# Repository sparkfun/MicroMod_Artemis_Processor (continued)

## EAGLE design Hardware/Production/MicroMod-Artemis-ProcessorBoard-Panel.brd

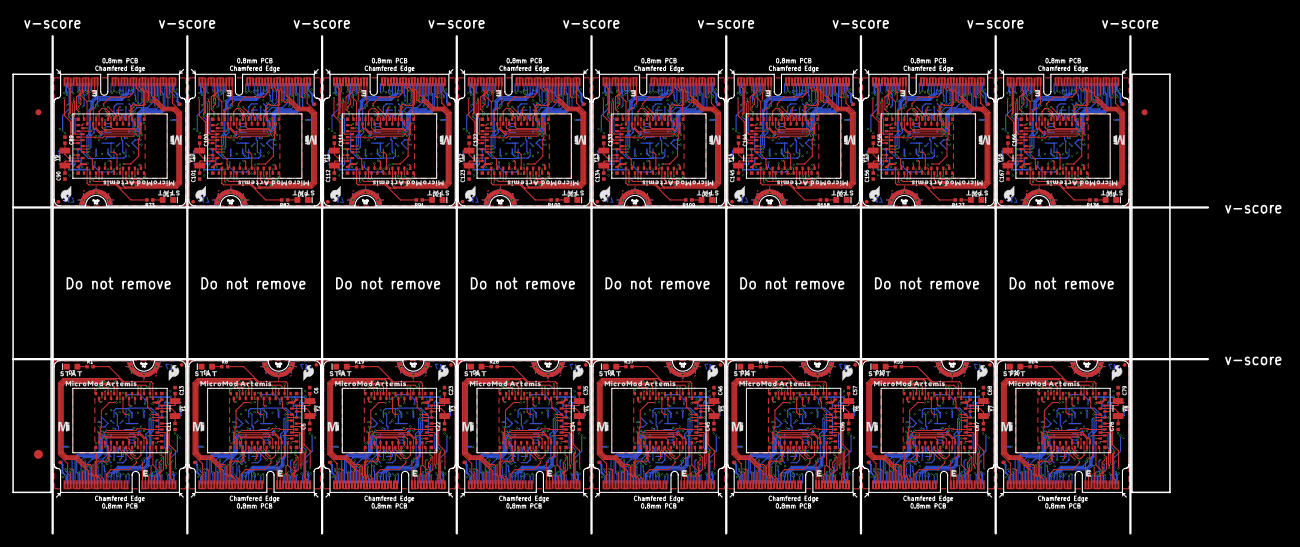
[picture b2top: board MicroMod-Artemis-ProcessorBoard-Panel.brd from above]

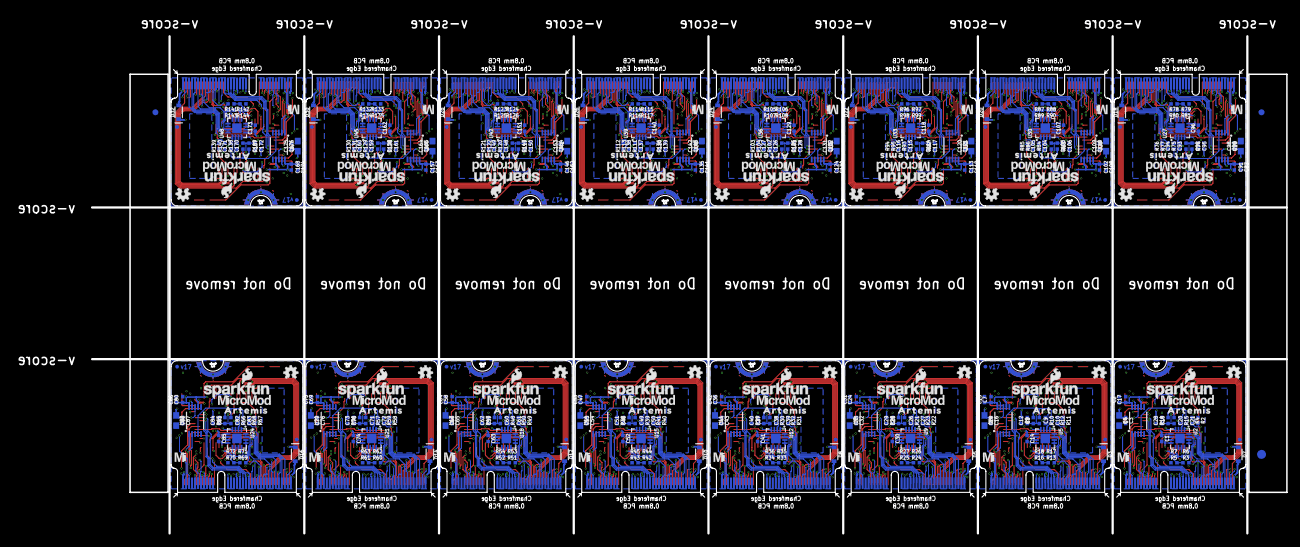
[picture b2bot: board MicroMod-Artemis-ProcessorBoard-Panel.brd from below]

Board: 4 copper layers, 199.6 x 83.1 mm, 646 parts (435 on the bottom side), 1008 nets.

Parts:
C1, C8, C9, C10, C14, C18, C20, C21, C25, C26, C27, C30, C37, C38, C39, C41, C48, C49, C50, C52, C59, C60, C61, C63, C70, C71, C72, C74, C81, C82, C83, C85, C92, C93, C94, C96, C103, C104, C105, C107, C114, C115, C116, C118, C125, C126, C127, C129, C136, C137, C138, C140, C147, C148, C149, C151, C158, C159, C160, C162, C169, C170, C171, C173: 0.1uF; 0402-TIGHT
C2, C15, C31, C42, C53, C64, C75, C86, C97, C108, C119, C130, C141, C152, C163, C174: 0.22uF; 0402-TIGHT
C3, C16, C32, C43, C54, C65, C76, C87, C98, C109, C120, C131, C142, C153, C164, C175: 1.0uF; 0402-TIGHT
C4, C19, C33, C44, C55, C66, C77, C88, C99, C110, C121, C132, C143, C154, C165, C176: 10uF; 0603
C5, C6, C11, C13, C22, C23, C34, C35, C45, C46, C56, C57, C67, C68, C78, C79, C89, C90, C100, C101, C111, C112, C122, C123, C133, C134, C144, C145, C155, C156, C166, C167: 15pF; 0402-TIGHT
C7, C17, C24, C36, C47, C58, C69, C80, C91, C102, C113, C124, C135, C146, C157, C168: 10nF; 0402-TIGHT
C12, C28, C29, C40, C51, C62, C73, C84, C95, C106, C117, C128, C139, C150, C161, C172: 1.0nF; 0402-TIGHT
D1, D2, D4, D6, D9, D11, D13, D15, D17, D19, D21, D23, D25, D27, D29, D31: BLUE; LED-0603
D3, D5, D7, D8, D10, D12, D14, D16, D18, D20, D22, D24, D26, D28, D30, D32: 1A/23V/620mV; SOD-323
E$1, E$2, E$3, E$4: FIDUCIAL-1X2
E$5, E$6: FIDUCIAL-1.5X3
FD1, FD2, FD3, FD4, FD5, FD6, FD7, FD8, FD9, FD10, FD11, FD12, FD13, FD14, FD15, FD16, FD17, FD18, FD19, FD20, FD21, FD22, FD23, FD24, FD25, FD26, FD27, FD28, FD29, FD30, FD31, FD32, FD33, FD34, FD35, FD36, FD37, FD38, FD39, FD40, FD41, FD42, FD43, FD44, FD45, FD46, FD47, FD48, FD49, FD50, FD51, FD52, FD53, FD54, FD55, FD56, FD57, FD58, FD59, FD60, FD61, FD62, FD63, FD64: FIDUCIALUFIDUCIAL; FIDUCIAL-MICRO
J1, J2, J3, J4, J5, J6, J7, J8, J9, J10, J11, J12, J13, J14, J15, J16: MICROMOD-2222; M.2-CARD-E-22
LOGO1, LOGO5, LOGO8, LOGO11, LOGO14, LOGO17, LOGO20, LOGO23, LOGO26, LOGO29, LOGO32, LOGO35, LOGO38, LOGO41, LOGO44, LOGO47: SFE_LOGO_NAME_FLAME.1_INCH; SFE_LOGO_NAME_FLAME_.1
LOGO2, LOGO6, LOGO9, LOGO12, LOGO15, LOGO18, LOGO21, LOGO24, LOGO27, LOGO30, LOGO33, LOGO36, LOGO39, LOGO42, LOGO45, LOGO48: SFE_LOGO_FLAME.1_INCH; SFE_LOGO_FLAME_.1
LOGO3, LOGO4, LOGO7, LOGO10, LOGO13, LOGO16, LOGO19, LOGO22, LOGO25, LOGO28, LOGO31, LOGO34, LOGO37, LOGO40, LOGO43, LOGO46: OSHW-LOGOMINI; OSHW-LOGO-MINI
R1, R8, R19, R28, R37, R46, R55, R64, R73, R82, R91, R100, R109, R118, R127, R136: 1k; 0402-TIGHT
R2, R3, R6, R9, R11, R13, R14, R17, R20, R22, R24, R26, R29, R31, R33, R35, R38, R40, R42, R44, R47, R49, R51, R53, R56, R58, R60, R62, R65, R67, R69, R71, R74, R76, R78, R80, R83, R85, R87, R89, R92, R94, R96, R98, R101, R103, R105, R107, R110, R112, R114, R116, R119, R121, R123, R125, R128, R130, R132, R134, R137, R139, R141, R143: 100k; 0402-TIGHT
R4, R5, R7, R12, R16, R18, R23, R25, R27, R32, R34, R36, R41, R43, R45, R50, R52, R54, R59, R61, R63, R68, R70, R72, R77, R79, R81, R86, R88, R90, R95, R97, R99, R104, R106, R108, R113, R115, R117, R122, R124, R126, R131, R133, R135, R140, R142, R144: 150k; 0402-TIGHT
R10, R15, R21, R30, R39, R48, R57, R66, R75, R84, R93, R102, R111, R120, R129, R138: 220K; 0402-TIGHT
U1, U3, U7, U10, U13, U16, U19, U22, U25, U28, U31, U34, U37, U40, U43, U46: ARTEMIS_MODULESMD; ARTEMIS_FP
U2, U5, U9, U12, U15, U18, U21, U24, U27, U30, U33, U36, U39, U42, U45, U48: TSV524; QFN-16
U4, U6, U8, U11, U14, U17, U20, U23, U26, U29, U32, U35, U38, U41, U44, U47: CH340E_MSOP10; MSOP10
U$1, U$2, U$4, U$7, U$13, U$15, U$19, U$21, U$25, U$27, U$31, U$33, U$37, U$39, U$43, U$45, U$49, U$51, U$55, U$57, U$61, U$63, U$67, U$69, U$73, U$75, U$79, U$81, U$85, U$87, U$91, U$93: MICROMOD_MI_LOGO_.35
U$3, U$5, U$14, U$20, U$26, U$32, U$38, U$44, U$50, U$56, U$62, U$68, U$74, U$80, U$86, U$92: MICROMOD_LOGO_.35
U$6, U$8, U$16, U$22, U$28, U$34, U$40, U$46, U$52, U$58, U$64, U$70, U$76, U$82, U$88, U$94: MICROMOD_ARTEMIS0
U$9, U$10, U$17, U$23, U$29, U$35, U$41, U$47, U$53, U$59, U$65, U$71, U$77, U$83, U$89, U$95: ARTEMIS0
U$11, U$12, U$18, U$24, U$30, U$36, U$42, U$48, U$54, U$60, U$66, U$72, U$78, U$84, U$90, U$96: STAT0
Y1, Y2, Y3, Y4, Y5, Y6, Y7, Y8, Y9, Y10, Y11, Y12, Y13, Y14, Y15, Y16: 32.768kHz; CRYSTAL-SMD-3.2X1.5MM

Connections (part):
3.3V: C2.1, C17.1, C18.1, D7.A, J1.2, J1.74, U6.7, U6.10
3.3V1: C7.1, C8.1, C15.1, D3.A, J2.2, J2.74, U4.7, U4.10
3.3V2: C24.1, C25.1, C31.1, D5.A, J3.2, J3.74, U8.7, U8.10
3.3V3: C36.1, C37.1, C42.1, D8.A, J4.2, J4.74, U11.7, U11.10
3.3V4: C47.1, C48.1, C53.1, D10.A, J5.2, J5.74, U14.7, U14.10
3.3V5: C58.1, C59.1, C64.1, D12.A, J6.2, J6.74, U17.7, U17.10
3.3V6: C69.1, C70.1, C75.1, D14.A, J7.2, J7.74, U20.7, U20.10
3.3V7: C80.1, C81.1, C86.1, D16.A, J8.2, J8.74, U23.7, U23.10
3.3V8: C91.1, C92.1, C97.1, D18.A, J9.2, J9.74, U26.7, U26.10
3.3V9: C102.1, C103.1, C108.1, D20.A, J10.2, J10.74, U29.7, U29.10
3.3V10: C113.1, C114.1, C119.1, D22.A, J11.2, J11.74, U32.7, U32.10
3.3V11: C124.1, C125.1, C130.1, D24.A, J12.2, J12.74, U35.7, U35.10
3.3V12: C135.1, C136.1, C141.1, D26.A, J13.2, J13.74, U38.7, U38.10
3.3V13: C146.1, C147.1, C152.1, D28.A, J14.2, J14.74, U41.7, U41.10
3.3V14: C157.1, C158.1, C163.1, D30.A, J15.2, J15.74, U44.7, U44.10
3.3V15: C168.1, C169.1, C174.1, D32.A, J16.2, J16.74, U47.7, U47.10
3.3V_EN: J1.4, U1.D3
3.3V_EN1: J2.4, U3.D3
3.3V_EN2: J3.4, U7.D3
3.3V_EN3: J4.4, U10.D3
3.3V_EN4: J5.4, U13.D3
3.3V_EN5: J6.4, U16.D3
3.3V_EN6: J7.4, U19.D3
3.3V_EN7: J8.4, U22.D3
3.3V_EN8: J9.4, U25.D3
3.3V_EN9: J10.4, U28.D3
3.3V_EN10: J11.4, U31.D3
3.3V_EN11: J12.4, U34.D3
3.3V_EN12: J13.4, U37.D3
3.3V_EN13: J14.4, U40.D3
3.3V_EN14: J15.4, U43.D3
3.3V_EN15: J16.4, U46.D3
!RESET!: C20.2, C28.1, J1.6, R14.1, U1.~RST
!RESET!1: C9.2, C12.1, J2.6, R9.1, U3.~RST
!RESET!2: C26.2, C29.1, J3.6, R20.1, U7.~RST
!RESET!3: C38.2, C40.1, J4.6, R29.1, U10.~RST
!RESET!4: C49.2, C51.1, J5.6, R38.1, U13.~RST
!RESET!5: C60.2, C62.1, J6.6, R47.1, U16.~RST
!RESET!6: C71.2, C73.1, J7.6, R56.1, U19.~RST
!RESET!7: C82.2, C84.1, J8.6, R65.1, U22.~RST
!RESET!8: C93.2, C95.1, J9.6, R74.1, U25.~RST
!RESET!9: C104.2, C106.1, J10.6, R83.1, U28.~RST
!RESET!10: C115.2, C117.1, J11.6, R92.1, U31.~RST
!RESET!11: C126.2, C128.1, J12.6, R101.1, U34.~RST
!RESET!12: C137.2, C139.1, J13.6, R110.1, U37.~RST
!RESET!13: C148.2, C150.1, J14.6, R119.1, U40.~RST
!RESET!14: C159.2, C161.1, J15.6, R128.1, U43.~RST
!RESET!15: C170.2, C172.1, J16.6, R137.1, U46.~RST
!RTS: C20.1, C21.1, U6.4
!RTS1: C9.1, C10.1, U4.4
!RTS2: C26.1, C27.1, U8.4
!RTS3: C38.1, C39.1, U11.4
!RTS4: C49.1, C50.1, U14.4
!RTS5: C60.1, C61.1, U17.4
!RTS6: C71.1, C72.1, U20.4
!RTS7: C82.1, C83.1, U23.4
!RTS8: C93.1, C94.1, U26.4
!RTS9: C104.1, C105.1, U29.4
!RTS10: C115.1, C116.1, U32.4
!RTS11: C126.1, C127.1, U35.4
!RTS12: C137.1, C138.1, U38.4
!RTS13: C148.1, C149.1, U41.4
!RTS14: C159.1, C160.1, U44.4
!RTS15: C170.1, C171.1, U47.4
ADC0: J1.34, U2.1
ADC0_BUFF1: R3.2, U2.15, U2.16
ADC0_BUFF2: R3.1, R5.2, U2.4
ADC0_BUFF3: R13.1, R16.2, U5.4
ADC0_BUFF4: R13.2, U5.15, U5.16
ADC0_BUFF5: R24.1, R25.2, U9.4
ADC0_BUFF6: R24.2, U9.15, U9.16
ADC0_BUFF7: R33.1, R34.2, U12.4
ADC0_BUFF8: R33.2, U12.15, U12.16
ADC0_BUFF9: R42.1, R43.2, U15.4
ADC0_BUFF10: R42.2, U15.15, U15.16
ADC0_BUFF11: R51.1, R52.2, U18.4
ADC0_BUFF12: R51.2, U18.15, U18.16
ADC0_BUFF13: R60.1, R61.2, U21.4
ADC0_BUFF14: R60.2, U21.15, U21.16
ADC0_BUFF15: R69.1, R70.2, U24.4
ADC0_BUFF16: R69.2, U24.15, U24.16
ADC0_BUFF17: R78.1, R79.2, U27.4
ADC0_BUFF18: R78.2, U27.15, U27.16
ADC0_BUFF19: R87.1, R88.2, U30.4
ADC0_BUFF20: R87.2, U30.15, U30.16
ADC0_BUFF21: R96.1, R97.2, U33.4
ADC0_BUFF22: R96.2, U33.15, U33.16
ADC0_BUFF23: R105.1, R106.2, U36.4
ADC0_BUFF24: R105.2, U36.15, U36.16
ADC0_BUFF25: R114.1, R115.2, U39.4
ADC0_BUFF26: R114.2, U39.15, U39.16
ADC0_BUFF27: R123.1, R124.2, U42.4
ADC0_BUFF28: R123.2, U42.15, U42.16
ADC0_BUFF29: R132.1, R133.2, U45.4
ADC0_BUFF30: R132.2, U45.15, U45.16
ADC0_BUFF31: R141.1, R142.2, U48.4
ADC0_BUFF32: R141.2, U48.15, U48.16
ADC1: J1.38, U2.12
ADC1_BUFF1: R17.1, R18.2, U5.9
ADC1_BUFF2: R6.1, R7.2, U2.9
ADC1_BUFF3: R26.1, R27.2, U9.9
ADC1_BUFF4: R35.1, R36.2, U12.9
ADC1_BUFF5: R44.1, R45.2, U15.9
ADC1_BUFF6: R53.1, R54.2, U18.9
ADC1_BUFF7: R62.1, R63.2, U21.9
ADC1_BUFF8: R71.1, R72.2, U24.9
ADC1_BUFF9: R80.1, R81.2, U27.9
ADC1_BUFF10: R89.1, R90.2, U30.9
ADC1_BUFF11: R98.1, R99.2, U33.9
ADC1_BUFF12: R107.1, R108.2, U36.9
ADC1_BUFF13: R116.1, R117.2, U39.9
ADC1_BUFF14: R125.1, R126.2, U42.9
ADC1_BUFF15: R134.1, R135.2, U45.9
ADC1_BUFF16: R143.1, R144.2, U48.9
ADC2: J2.34, U5.1
ADC3: J2.38, U5.12
ADC4: J3.34, U9.1
ADC5: J3.38, U9.12
ADC6: J4.34, U12.1
ADC7: J4.38, U12.12
ADC8: J5.34, U15.1
ADC9: J5.38, U15.12
ADC10: J6.34, U18.1
ADC11: J6.38, U18.12
ADC12: J7.34, U21.1
ADC13: J7.38, U21.12
ADC14: J8.34, U24.1
ADC15: J8.38, U24.12
ADC16: J9.34, U27.1
ADC17: J9.38, U27.12
ADC18: J10.34, U30.1
ADC19: J10.38, U30.12
ADC20: J11.34, U33.1
ADC21: J11.38, U33.12
ADC22: J12.34, U36.1
ADC23: J12.38, U36.12
ADC24: J13.34, U39.1
ADC25: J13.38, U39.12
ADC26: J14.34, U42.1
ADC27: J14.38, U42.12
ADC28: J15.34, U45.1
ADC29: J15.38, U45.12
ADC30: J16.34, U48.1
ADC31: J16.38, U48.12
ADC_BUFF1: R6.2, U2.13, U2.14
ADC_BUFF2: R17.2, U5.13, U5.14
ADC_BUFF3: R26.2, U9.13, U9.14
ADC_BUFF4: R35.2, U12.13, U12.14
ADC_BUFF5: R44.2, U15.13, U15.14
ADC_BUFF6: R53.2, U18.13, U18.14
ADC_BUFF7: R62.2, U21.13, U21.14
ADC_BUFF8: R71.2, U24.13, U24.14
ADC_BUFF9: R80.2, U27.13, U27.14
ADC_BUFF10: R89.2, U30.13, U30.14
ADC_BUFF11: R98.2, U33.13, U33.14
ADC_BUFF12: R107.2, U36.13, U36.14
ADC_BUFF13: R116.2, U39.13, U39.14
ADC_BUFF14: R125.2, U42.13, U42.14
ADC_BUFF15: R134.2, U45.13, U45.14
ADC_BUFF16: R143.2, U48.13, U48.14
ADC_D+: J1.63, U1.~AD13
ADC_D+1: J2.63, U3.~AD13
ADC_D+2: J3.63, U7.~AD13
ADC_D+3: J4.63, U10.~AD13
ADC_D+4: J5.63, U13.~AD13
ADC_D+5: J6.63, U16.~AD13
ADC_D+6: J7.63, U19.~AD13
ADC_D+7: J8.63, U22.~AD13
ADC_D+8: J9.63, U25.~AD13
ADC_D+9: J10.63, U28.~AD13
ADC_D+10: J11.63, U31.~AD13
ADC_D+11: J12.63, U34.~AD13
ADC_D+12: J13.63, U37.~AD13
ADC_D+13: J14.63, U40.~AD13
ADC_D+14: J15.63, U43.~AD13
ADC_D+15: J16.63, U46.~AD13
BATT_VIN/1: J2.49, R11.2
BATT_VIN/2: J3.49, R22.2
BATT_VIN/3: J1.49, R2.2
BATT_VIN/4: J4.49, R31.2
BATT_VIN/5: J5.49, R40.2
BATT_VIN/6: J6.49, R49.2
BATT_VIN/7: J7.49, R58.2
BATT_VIN/8: J8.49, R67.2
BATT_VIN/9: J9.49, R76.2
BATT_VIN/10: J10.49, R85.2
BATT_VIN/11: J11.49, R94.2
BATT_VIN/12: J12.49, R103.2
BATT_VIN/13: J13.49, R112.2
BATT_VIN/14: J14.49, R121.2
BATT_VIN/15: J15.49, R130.2
BATT_VIN/16: J16.49, R139.2
BOOT: C21.2, J1.11, R15.2, U1.BOOT
BOOT1: C10.2, J2.11, R10.2, U3.BOOT
BOOT2: C27.2, J3.11, R21.2, U7.BOOT
BOOT3: C39.2, J4.11, R30.2, U10.BOOT
BOOT4: C50.2, J5.11, R39.2, U13.BOOT
BOOT5: C61.2, J6.11, R48.2, U16.BOOT
BOOT6: C72.2, J7.11, R57.2, U19.BOOT
BOOT7: C83.2, J8.11, R66.2, U22.BOOT
BOOT8: C94.2, J9.11, R75.2, U25.BOOT
BOOT9: C105.2, J10.11, R84.2, U28.BOOT
BOOT10: C116.2, J11.11, R93.2, U31.BOOT
BOOT11: C127.2, J12.11, R102.2, U34.BOOT
BOOT12: C138.2, J13.11, R111.2, U37.BOOT
BOOT13: C149.2, J14.11, R120.2, U40.BOOT
BOOT14: C160.2, J15.11, R129.2, U43.BOOT
BOOT15: C171.2, J16.11, R138.2, U46.BOOT
CAM_MCLK: J1.56, J1.58, U1.~D18
CAM_MCLK1: J2.56, J2.58, U3.~D18
CAM_MCLK2: J3.56, J3.58, U7.~D18
CAM_MCLK3: J4.56, J4.58, U10.~D18
CAM_MCLK4: J5.56, J5.58, U13.~D18
CAM_MCLK5: J6.56, J6.58, U16.~D18
CAM_MCLK6: J7.56, J7.58, U19.~D18
CAM_MCLK7: J8.56, J8.58, U22.~D18
CAM_MCLK8: J9.56, J9.58, U25.~D18
CAM_MCLK9: J10.56, J10.58, U28.~D18
CAM_MCLK10: J11.56, J11.58, U31.~D18
CAM_MCLK11: J12.56, J12.58, U34.~D18
CAM_MCLK12: J13.56, J13.58, U37.~D18
CAM_MCLK13: J14.56, J14.58, U40.~D18
CAM_MCLK14: J15.56, J15.58, U43.~D18
CAM_MCLK15: J16.56, J16.58, U46.~D18
CAM_PCLK: J1.54, U1.~AD11
CAM_PCLK1: J2.54, U3.~AD11
CAM_PCLK2: J3.54, U7.~AD11
CAM_PCLK3: J4.54, U10.~AD11
CAM_PCLK4: J5.54, U13.~AD11
CAM_PCLK5: J6.54, U16.~AD11
CAM_PCLK6: J7.54, U19.~AD11
CAM_PCLK7: J8.54, U22.~AD11
CAM_PCLK8: J9.54, U25.~AD11
CAM_PCLK9: J10.54, U28.~AD11
CAM_PCLK10: J11.54, U31.~AD11
CAM_PCLK11: J12.54, U34.~AD11
CAM_PCLK12: J13.54, U37.~AD11
CAM_PCLK13: J14.54, U40.~AD11
CAM_PCLK14: J15.54, U43.~AD11
CAM_PCLK15: J16.54, U46.~AD11
CTS1: J1.15, U1.D17
CTS2: J2.15, U3.D17
CTS3: J3.15, U7.D17
CTS4: J4.15, U10.D17
CTS5: J5.15, U13.D17
CTS6: J6.15, U16.D17
CTS7: J7.15, U19.D17
CTS8: J8.15, U22.D17
CTS9: J9.15, U25.D17
CTS10: J10.15, U28.D17
CTS11: J11.15, U31.D17
CTS12: J12.15, U34.D17
CTS13: J13.15, U37.D17
CTS14: J14.15, U40.D17
CTS15: J15.15, U43.D17
CTS16: J16.15, U46.D17
D0: J1.10, U1.D0
D1: J1.18, U1.D1
D2: J2.10, U3.D0
D3: J2.18, U3.D1
D4: J3.10, U7.D0
D5: J3.18, U7.D1
D6: J4.10, U10.D0
D7: J4.18, U10.D1
D8: J5.10, U13.D0
D9: J5.18, U13.D1
D10: J6.10, U16.D0
D11: J6.18, U16.D1
D12: J7.10, U19.D0
D13: J7.18, U19.D1
D14: J8.10, U22.D0
D15: J8.18, U22.D1
D16: J9.10, U25.D0
D17: J9.18, U25.D1
D18: J10.10, U28.D0
D19: J10.18, U28.D1
D20: J11.10, U31.D0
D21: J11.18, U31.D1
D22: J12.10, U34.D0
D23: J12.18, U34.D1
D24: J13.10, U37.D0
D25: J13.18, U37.D1
D26: J14.10, U40.D0
D27: J14.18, U40.D1
D28: J15.10, U43.D0
D29: J15.18, U43.D1
D30: J16.10, U46.D0
D31: J16.18, U46.D1
GND: C1.2, C2.2, C3.2, C4.2, C11.1, C13.1, C17.2, C18.2, C28.2, D2.C, J1.1, J1.7, J1.33, J1.36, J1.39, J1.45, J1.75, J1.GND1, J1.GND2, J1.GND3, R4.1, R5.1, R7.1, R15.1, U1.GND@1, U1.GND@22, U1.GND@38, U1.GND@39, U1.GND@47, U1.GND@59, U2.11, U6.3
GND1: C5.1, C6.1, C7.2, C8.2, C12.2, C14.2, C15.2, C16.2, C19.2, D1.C, J2.1, J2.7, J2.33, J2.36, J2.39, J2.45, J2.75, J2.GND1, J2.GND2, J2.GND3, R10.1, R12.1, R16.1, R18.1, U3.GND@1, U3.GND@22, U3.GND@38, U3.GND@39, U3.GND@47, U3.GND@59, U4.3, U5.11
GND2: C22.1, C23.1, C24.2, C25.2, C29.2, C30.2, C31.2, C32.2, C33.2, D4.C, J3.1, J3.7, J3.33, J3.36, J3.39, J3.45, J3.75, J3.GND1, J3.GND2, J3.GND3, R21.1, R23.1, R25.1, R27.1, U7.GND@1, U7.GND@22, U7.GND@38, U7.GND@39, U7.GND@47, U7.GND@59, U8.3, U9.11
GND3: C34.1, C35.1, C36.2, C37.2, C40.2, C41.2, C42.2, C43.2, C44.2, D6.C, J4.1, J4.7, J4.33, J4.36, J4.39, J4.45, J4.75, J4.GND1, J4.GND2, J4.GND3, R30.1, R32.1, R34.1, R36.1, U10.GND@1, U10.GND@22, U10.GND@38, U10.GND@39, U10.GND@47, U10.GND@59, U11.3, U12.11
GND4: C45.1, C46.1, C47.2, C48.2, C51.2, C52.2, C53.2, C54.2, C55.2, D9.C, J5.1, J5.7, J5.33, J5.36, J5.39, J5.45, J5.75, J5.GND1, J5.GND2, J5.GND3, R39.1, R41.1, R43.1, R45.1, U13.GND@1, U13.GND@22, U13.GND@38, U13.GND@39, U13.GND@47, U13.GND@59, U14.3, U15.11
GND5: C56.1, C57.1, C58.2, C59.2, C62.2, C63.2, C64.2, C65.2, C66.2, D11.C, J6.1, J6.7, J6.33, J6.36, J6.39, J6.45, J6.75, J6.GND1, J6.GND2, J6.GND3, R48.1, R50.1, R52.1, R54.1, U16.GND@1, U16.GND@22, U16.GND@38, U16.GND@39, U16.GND@47, U16.GND@59, U17.3, U18.11
GND6: C67.1, C68.1, C69.2, C70.2, C73.2, C74.2, C75.2, C76.2, C77.2, D13.C, J7.1, J7.7, J7.33, J7.36, J7.39, J7.45, J7.75, J7.GND1, J7.GND2, J7.GND3, R57.1, R59.1, R61.1, R63.1, U19.GND@1, U19.GND@22, U19.GND@38, U19.GND@39, U19.GND@47, U19.GND@59, U20.3, U21.11
GND7: C78.1, C79.1, C80.2, C81.2, C84.2, C85.2, C86.2, C87.2, C88.2, D15.C, J8.1, J8.7, J8.33, J8.36, J8.39, J8.45, J8.75, J8.GND1, J8.GND2, J8.GND3, R66.1, R68.1, R70.1, R72.1, U22.GND@1, U22.GND@22, U22.GND@38, U22.GND@39, U22.GND@47, U22.GND@59, U23.3, U24.11
GND8: C89.1, C90.1, C91.2, C92.2, C95.2, C96.2, C97.2, C98.2, C99.2, D17.C, J9.1, J9.7, J9.33, J9.36, J9.39, J9.45, J9.75, J9.GND1, J9.GND2, J9.GND3, R75.1, R77.1, R79.1, R81.1, U25.GND@1, U25.GND@22, U25.GND@38, U25.GND@39, U25.GND@47, U25.GND@59, U26.3, U27.11
GND9: C100.1, C101.1, C102.2, C103.2, C106.2, C107.2, C108.2, C109.2, C110.2, D19.C, J10.1, J10.7, J10.33, J10.36, J10.39, J10.45, J10.75, J10.GND1, J10.GND2, J10.GND3, R84.1, R86.1, R88.1, R90.1, U28.GND@1, U28.GND@22, U28.GND@38, U28.GND@39, U28.GND@47, U28.GND@59, U29.3, U30.11
GND10: C111.1, C112.1, C113.2, C114.2, C117.2, C118.2, C119.2, C120.2, C121.2, D21.C, J11.1, J11.7, J11.33, J11.36, J11.39, J11.45, J11.75, J11.GND1, J11.GND2, J11.GND3, R93.1, R95.1, R97.1, R99.1, U31.GND@1, U31.GND@22, U31.GND@38, U31.GND@39, U31.GND@47, U31.GND@59, U32.3, U33.11
GND11: C122.1, C123.1, C124.2, C125.2, C128.2, C129.2, C130.2, C131.2, C132.2, D23.C, J12.1, J12.7, J12.33, J12.36, J12.39, J12.45, J12.75, J12.GND1, J12.GND2, J12.GND3, R102.1, R104.1, R106.1, R108.1, U34.GND@1, U34.GND@22, U34.GND@38, U34.GND@39, U34.GND@47, U34.GND@59, U35.3, U36.11
GND12: C133.1, C134.1, C135.2, C136.2, C139.2, C140.2, C141.2, C142.2, C143.2, D25.C, J13.1, J13.7, J13.33, J13.36, J13.39, J13.45, J13.75, J13.GND1, J13.GND2, J13.GND3, R111.1, R113.1, R115.1, R117.1, U37.GND@1, U37.GND@22, U37.GND@38, U37.GND@39, U37.GND@47, U37.GND@59, U38.3, U39.11
GND13: C144.1, C145.1, C146.2, C147.2, C150.2, C151.2, C152.2, C153.2, C154.2, D27.C, J14.1, J14.7, J14.33, J14.36, J14.39, J14.45, J14.75, J14.GND1, J14.GND2, J14.GND3, R120.1, R122.1, R124.1, R126.1, U40.GND@1, U40.GND@22, U40.GND@38, U40.GND@39, U40.GND@47, U40.GND@59, U41.3, U42.11
GND14: C155.1, C156.1, C157.2, C158.2, C161.2, C162.2, C163.2, C164.2, C165.2, D29.C, J15.1, J15.7, J15.33, J15.36, J15.39, J15.45, J15.75, J15.GND1, J15.GND2, J15.GND3, R129.1, R131.1, R133.1, R135.1, U43.GND@1, U43.GND@22, U43.GND@38, U43.GND@39, U43.GND@47, U43.GND@59, U44.3, U45.11
GND15: C166.1, C167.1, C168.2, C169.2, C172.2, C173.2, C174.2, C175.2, C176.2, D31.C, J16.1, J16.7, J16.33, J16.36, J16.39, J16.45, J16.75, J16.GND1, J16.GND2, J16.GND3, R138.1, R140.1, R142.1, R144.1, U46.GND@1, U46.GND@22, U46.GND@38, U46.GND@39, U46.GND@47, U46.GND@59, U47.3, U48.11
GPIO0: J1.40, U1.AD16
GPIO1: J1.42, U1.~AD33/SWO
GPIO2: J1.44, U1.AD34
GPIO3: J1.46, U1.~D27
GPIO4: J1.48, U1.~D28
GPIO5: J1.73, U1.~AD29
GPIO6: J1.71, U1.D14
GPIO7: J1.69, U1.D15
GPIO8: J2.73, U3.~AD29
GPIO9: J2.69, U3.D15
GPIO10: J2.71, U3.D14
GPIO11: J2.42, U3.~AD33/SWO
GPIO12: J2.46, U3.~D27
GPIO13: J2.44, U3.AD34
GPIO14: J2.48, U3.~D28
GPIO15: J2.40, U3.AD16
GPIO16: J3.73, U7.~AD29
GPIO17: J3.69, U7.D15
GPIO18: J3.71, U7.D14
GPIO19: J3.42, U7.~AD33/SWO
GPIO20: J3.46, U7.~D27
GPIO21: J3.44, U7.AD34
GPIO22: J3.48, U7.~D28
GPIO23: J3.40, U7.AD16
GPIO24: J4.73, U10.~AD29
GPIO25: J4.69, U10.D15
GPIO26: J4.71, U10.D14
GPIO27: J4.42, U10.~AD33/SWO
GPIO28: J4.46, U10.~D27
GPIO29: J4.44, U10.AD34
GPIO30: J4.48, U10.~D28
GPIO31: J4.40, U10.AD16
GPIO32: J5.73, U13.~AD29
GPIO33: J5.69, U13.D15
GPIO34: J5.71, U13.D14
GPIO35: J5.42, U13.~AD33/SWO
GPIO36: J5.46, U13.~D27
GPIO37: J5.44, U13.AD34
GPIO38: J5.48, U13.~D28
GPIO39: J5.40, U13.AD16
GPIO40: J6.73, U16.~AD29
GPIO41: J6.69, U16.D15
GPIO42: J6.71, U16.D14
GPIO43: J6.42, U16.~AD33/SWO
GPIO44: J6.46, U16.~D27
GPIO45: J6.44, U16.AD34
GPIO46: J6.48, U16.~D28
GPIO47: J6.40, U16.AD16
GPIO48: J7.73, U19.~AD29
GPIO49: J7.69, U19.D15
GPIO50: J7.71, U19.D14
GPIO51: J7.42, U19.~AD33/SWO
GPIO52: J7.46, U19.~D27
GPIO53: J7.44, U19.AD34
GPIO54: J7.48, U19.~D28
GPIO55: J7.40, U19.AD16
GPIO56: J8.73, U22.~AD29
GPIO57: J8.69, U22.D15
GPIO58: J8.71, U22.D14
GPIO59: J8.42, U22.~AD33/SWO
GPIO60: J8.46, U22.~D27
GPIO61: J8.44, U22.AD34
GPIO62: J8.48, U22.~D28
GPIO63: J8.40, U22.AD16
GPIO64: J9.73, U25.~AD29
GPIO65: J9.69, U25.D15
GPIO66: J9.71, U25.D14
GPIO67: J9.42, U25.~AD33/SWO
GPIO68: J9.46, U25.~D27
GPIO69: J9.44, U25.AD34
GPIO70: J9.48, U25.~D28
GPIO71: J9.40, U25.AD16
GPIO72: J10.73, U28.~AD29
GPIO73: J10.69, U28.D15
GPIO74: J10.71, U28.D14
GPIO75: J10.42, U28.~AD33/SWO
GPIO76: J10.46, U28.~D27
GPIO77: J10.44, U28.AD34
GPIO78: J10.48, U28.~D28
GPIO79: J10.40, U28.AD16
GPIO80: J11.73, U31.~AD29
GPIO81: J11.69, U31.D15
GPIO82: J11.71, U31.D14
GPIO83: J11.42, U31.~AD33/SWO
GPIO84: J11.46, U31.~D27
GPIO85: J11.44, U31.AD34
GPIO86: J11.48, U31.~D28
GPIO87: J11.40, U31.AD16
GPIO88: J12.73, U34.~AD29
GPIO89: J12.69, U34.D15
GPIO90: J12.71, U34.D14
GPIO91: J12.42, U34.~AD33/SWO
GPIO92: J12.46, U34.~D27
GPIO93: J12.44, U34.AD34
GPIO94: J12.48, U34.~D28
GPIO95: J12.40, U34.AD16
GPIO96: J13.73, U37.~AD29
GPIO97: J13.69, U37.D15
GPIO98: J13.71, U37.D14
GPIO99: J13.42, U37.~AD33/SWO
GPIO100: J13.46, U37.~D27
GPIO101: J13.44, U37.AD34
GPIO102: J13.48, U37.~D28
GPIO103: J13.40, U37.AD16
GPIO104: J14.73, U40.~AD29
GPIO105: J14.69, U40.D15
GPIO106: J14.71, U40.D14
GPIO107: J14.42, U40.~AD33/SWO
GPIO108: J14.46, U40.~D27
GPIO109: J14.44, U40.AD34
GPIO110: J14.48, U40.~D28
GPIO111: J14.40, U40.AD16
GPIO112: J15.73, U43.~AD29
GPIO113: J15.69, U43.D15
GPIO114: J15.71, U43.D14
GPIO115: J15.42, U43.~AD33/SWO
GPIO116: J15.46, U43.~D27
GPIO117: J15.44, U43.AD34
GPIO118: J15.48, U43.~D28
GPIO119: J15.40, U43.AD16
GPIO120: J16.73, U46.~AD29
GPIO121: J16.69, U46.D15
GPIO122: J16.71, U46.D14
GPIO123: J16.42, U46.~AD33/SWO
GPIO124: J16.46, U46.~D27
GPIO125: J16.44, U46.AD34
GPIO126: J16.48, U46.~D28
GPIO127: J16.40, U46.AD16
I2C_!INT!: J1.16, U1.D2
I2C_!INT!1: J2.16, U3.D2
I2C_!INT!2: J3.16, U7.D2
I2C_!INT!3: J4.16, U10.D2
I2C_!INT!4: J5.16, U13.D2
I2C_!INT!5: J6.16, U16.D2
I2C_!INT!6: J7.16, U19.D2
I2C_!INT!7: J8.16, U22.D2
I2C_!INT!8: J9.16, U25.D2
I2C_!INT!9: J10.16, U28.D2
I2C_!INT!10: J11.16, U31.D2
I2C_!INT!11: J12.16, U34.D2
I2C_!INT!12: J13.16, U37.D2
I2C_!INT!13: J14.16, U40.D2
I2C_!INT!14: J15.16, U43.D2
I2C_!INT!15: J16.16, U46.D2
LED_BUILTIN: R1.2, U1.~D19
LED_BUILTIN1: R8.2, U3.~D19
LED_BUILTIN2: R19.2, U7.~D19
LED_BUILTIN3: R28.2, U10.~D19
LED_BUILTIN4: R37.2, U13.~D19
LED_BUILTIN5: R46.2, U16.~D19
LED_BUILTIN6: R55.2, U19.~D19
LED_BUILTIN7: R64.2, U22.~D19
LED_BUILTIN8: R73.2, U25.~D19
LED_BUILTIN9: R82.2, U28.~D19
LED_BUILTIN10: R91.2, U31.~D19
LED_BUILTIN11: R100.2, U34.~D19
LED_BUILTIN12: R109.2, U37.~D19
LED_BUILTIN13: R118.2, U40.~D19
LED_BUILTIN14: R127.2, U43.~D19
LED_BUILTIN15: R136.2, U46.~D19
unnamed: C5.2, U3.XO, Y2.P$2
unnamed: D2.A, R1.1
unnamed: D1.A, R8.1
unnamed: C6.2, U3.XI, Y2.P$1
unnamed: C13.2, U1.XI, Y1.P$1
unnamed: C22.2, U7.XO, Y3.P$2
unnamed: C11.2, U1.XO, Y1.P$2
unnamed: D4.A, R19.1
unnamed: C23.2, U7.XI, Y3.P$1
unnamed: C34.2, U10.XO, Y4.P$2
unnamed: D6.A, R28.1
unnamed: C35.2, U10.XI, Y4.P$1
unnamed: C45.2, U13.XO, Y5.P$2
unnamed: D9.A, R37.1
unnamed: C46.2, U13.XI, Y5.P$1
unnamed: C56.2, U16.XO, Y6.P$2
unnamed: D11.A, R46.1
unnamed: C57.2, U16.XI, Y6.P$1
unnamed: C67.2, U19.XO, Y7.P$2
unnamed: D13.A, R55.1
unnamed: C68.2, U19.XI, Y7.P$1
unnamed: C78.2, U22.XO, Y8.P$2
unnamed: D15.A, R64.1
unnamed: C79.2, U22.XI, Y8.P$1
unnamed: C89.2, U25.XO, Y9.P$2
unnamed: D17.A, R73.1
unnamed: C90.2, U25.XI, Y9.P$1
unnamed: C100.2, U28.XO, Y10.P$2
unnamed: D19.A, R82.1
unnamed: C101.2, U28.XI, Y10.P$1
unnamed: C111.2, U31.XO, Y11.P$2
unnamed: D21.A, R91.1
unnamed: C112.2, U31.XI, Y11.P$1
unnamed: C122.2, U34.XO, Y12.P$2
unnamed: D23.A, R100.1
unnamed: C123.2, U34.XI, Y12.P$1
unnamed: C133.2, U37.XO, Y13.P$2
unnamed: D25.A, R109.1
unnamed: C134.2, U37.XI, Y13.P$1
unnamed: C144.2, U40.XO, Y14.P$2
unnamed: D27.A, R118.1
unnamed: C145.2, U40.XI, Y14.P$1
unnamed: C155.2, U43.XO, Y15.P$2
unnamed: D29.A, R127.1
unnamed: C156.2, U43.XI, Y15.P$1
unnamed: C166.2, U46.XO, Y16.P$2
unnamed: D31.A, R136.1
unnamed: C167.2, U46.XI, Y16.P$1
PDM_CLK: J1.50, U1.~D37
PDM_CLK1: J2.50, U3.~D37
PDM_CLK2: J3.50, U7.~D37
PDM_CLK3: J4.50, U10.~D37
PDM_CLK4: J5.50, U13.~D37
PDM_CLK5: J6.50, U16.~D37
PDM_CLK6: J7.50, U19.~D37
PDM_CLK7: J8.50, U22.~D37
PDM_CLK8: J9.50, U25.~D37
PDM_CLK9: J10.50, U28.~D37
PDM_CLK10: J11.50, U31.~D37
PDM_CLK11: J12.50, U34.~D37
PDM_CLK12: J13.50, U37.~D37
PDM_CLK13: J14.50, U40.~D37
PDM_CLK14: J15.50, U43.~D37
PDM_CLK15: J16.50, U46.~D37
PDM_DATA: J1.52, U1.D36
PDM_DATA1: J2.52, U3.D36
PDM_DATA2: J3.52, U7.D36
PDM_DATA3: J4.52, U10.D36
PDM_DATA4: J5.52, U13.D36
PDM_DATA5: J6.52, U16.D36
PDM_DATA6: J7.52, U19.D36
PDM_DATA7: J8.52, U22.D36
PDM_DATA8: J9.52, U25.D36
PDM_DATA9: J10.52, U28.D36
PDM_DATA10: J11.52, U31.D36
PDM_DATA11: J12.52, U34.D36
PDM_DATA12: J13.52, U37.D36
PDM_DATA13: J14.52, U40.D36
PDM_DATA14: J15.52, U43.D36
PDM_DATA15: J16.52, U46.D36
PWM0: J1.32, U1.~D44
PWM1: J1.47, U1.~D45
PWM2: J2.32, U3.~D44
PWM3: J2.47, U3.~D45
PWM4: J3.32, U7.~D44
PWM5: J3.47, U7.~D45
PWM6: J4.32, U10.~D44
PWM7: J4.47, U10.~D45
PWM8: J5.32, U13.~D44
PWM9: J5.47, U13.~D45
PWM10: J6.32, U16.~D44
PWM11: J6.47, U16.~D45
PWM12: J7.32, U19.~D44
PWM13: J7.47, U19.~D45
PWM14: J8.32, U22.~D44
PWM15: J8.47, U22.~D45
PWM16: J9.32, U25.~D44
PWM17: J9.47, U25.~D45
PWM18: J10.32, U28.~D44
PWM19: J10.47, U28.~D45
PWM20: J11.32, U31.~D44
PWM21: J11.47, U31.~D45
PWM22: J12.32, U34.~D44
PWM23: J12.47, U34.~D45
PWM24: J13.32, U37.~D44
PWM25: J13.47, U37.~D45
PWM26: J14.32, U40.~D44
PWM27: J14.47, U40.~D45
PWM28: J15.32, U43.~D44
PWM29: J15.47, U43.~D45
PWM30: J16.32, U46.~D44
PWM31: J16.47, U46.~D45
QSPI1: J1.66, U1.~D26
QSPI2: J1.68, U1.~D4
QSPI3: J2.66, U3.~D26
QSPI4: J2.68, U3.~D4
QSPI5: J3.66, U7.~D26
QSPI6: J3.68, U7.~D4
QSPI7: J4.66, U10.~D26
QSPI8: J4.68, U10.~D4
QSPI9: J5.66, U13.~D26
QSPI10: J5.68, U13.~D4
QSPI11: J6.66, U16.~D26
QSPI12: J6.68, U16.~D4
QSPI13: J7.66, U19.~D26
QSPI14: J7.68, U19.~D4
QSPI15: J8.66, U22.~D26
QSPI16: J8.68, U22.~D4
QSPI17: J9.66, U25.~D26
QSPI18: J9.68, U25.~D4
QSPI19: J10.66, U28.~D26
QSPI20: J10.68, U28.~D4
QSPI21: J11.66, U31.~D26
QSPI22: J11.68, U31.~D4
QSPI23: J12.66, U34.~D26
QSPI24: J12.68, U34.~D4
QSPI25: J13.66, U37.~D26
QSPI26: J13.68, U37.~D4
QSPI27: J14.66, U40.~D26
QSPI28: J14.68, U40.~D4
QSPI29: J15.66, U43.~D26
QSPI30: J15.68, U43.~D4
QSPI31: J16.66, U46.~D26
QSPI32: J16.68, U46.~D4
RTS1: J1.13, U1.D10
RTS2: J2.13, U3.D10
RTS3: J3.13, U7.D10
RTS4: J4.13, U10.D10
RTS5: J5.13, U13.D10
RTS6: J6.13, U16.D10
RTS7: J7.13, U19.D10
RTS8: J8.13, U22.D10
RTS9: J9.13, U25.D10
RTS10: J10.13, U28.D10
RTS11: J11.13, U31.D10
RTS12: J12.13, U34.D10
RTS13: J13.13, U37.D10
RTS14: J14.13, U40.D10
RTS15: J15.13, U43.D10
RTS16: J16.13, U46.D10
RX1: J1.19, U1.~D25
RX2: J2.19, U3.~D25
RX3: J3.19, U7.~D25
RX4: J4.19, U10.~D25
RX5: J5.19, U13.~D25
RX6: J6.19, U16.~D25
RX7: J7.19, U19.~D25
RX8: J8.19, U22.~D25
RX9: J9.19, U25.~D25
RX10: J10.19, U28.~D25
RX11: J11.19, U31.~D25
RX12: J12.19, U34.~D25
RX13: J13.19, U37.~D25
RX14: J14.19, U40.~D25
RX15: J15.19, U43.~D25
RX16: J16.19, U46.~D25
RXI-0: U1.RXI-0, U6.8
RXI-1: U3.RXI-0, U4.8
RXI-2: U7.RXI-0, U8.8
RXI-3: U10.RXI-0, U11.8
RXI-4: U13.RXI-0, U14.8
RXI-5: U16.RXI-0, U17.8
RXI-6: U19.RXI-0, U20.8
RXI-7: U22.RXI-0, U23.8
RXI-8: U25.RXI-0, U26.8
RXI-9: U28.RXI-0, U29.8
RXI-10: U31.RXI-0, U32.8
RXI-11: U34.RXI-0, U35.8
RXI-12: U37.RXI-0, U38.8
RXI-13: U40.RXI-0, U41.8
RXI-14: U43.RXI-0, U44.8
RXI-15: U46.RXI-0, U47.8
SCALED_ADC0: U1.~AD32, U2.5, U2.6
SCALED_ADC1: U1.~AD35, U2.7, U2.8
SCALED_ADC2: U3.~AD32, U5.5, U5.6
SCALED_ADC3: U3.~AD35, U5.7, U5.8
SCALED_ADC4: U7.~AD32, U9.5, U9.6
SCALED_ADC5: U7.~AD35, U9.7, U9.8
SCALED_ADC6: U10.~AD32, U12.5, U12.6
SCALED_ADC7: U10.~AD35, U12.7, U12.8
SCALED_ADC8: U13.~AD32, U15.5, U15.6
SCALED_ADC9: U13.~AD35, U15.7, U15.8
SCALED_ADC10: U16.~AD32, U18.5, U18.6
SCALED_ADC11: U16.~AD35, U18.7, U18.8
SCALED_ADC12: U19.~AD32, U21.5, U21.6
SCALED_ADC13: U19.~AD35, U21.7, U21.8
SCALED_ADC14: U22.~AD32, U24.5, U24.6
SCALED_ADC15: U22.~AD35, U24.7, U24.8
SCALED_ADC16: U25.~AD32, U27.5, U27.6
SCALED_ADC17: U25.~AD35, U27.7, U27.8
SCALED_ADC18: U28.~AD32, U30.5, U30.6
SCALED_ADC19: U28.~AD35, U30.7, U30.8
SCALED_ADC20: U31.~AD32, U33.5, U33.6
SCALED_ADC21: U31.~AD35, U33.7, U33.8
SCALED_ADC22: U34.~AD32, U36.5, U36.6
SCALED_ADC23: U34.~AD35, U36.7, U36.8
SCALED_ADC24: U37.~AD32, U39.5, U39.6
SCALED_ADC25: U37.~AD35, U39.7, U39.8
SCALED_ADC26: U40.~AD32, U42.5, U42.6
SCALED_ADC27: U40.~AD35, U42.7, U42.8
SCALED_ADC28: U43.~AD32, U45.5, U45.6
SCALED_ADC29: U43.~AD35, U45.7, U45.8
SCALED_ADC30: U46.~AD32, U48.5, U48.6
SCALED_ADC31: U46.~AD35, U48.7, U48.8
SCALED_BATT_VIN/1: R11.1, R12.2, U3.~AD31
SCALED_BATT_VIN/2: R22.1, R23.2, U7.~AD31
SCALED_BATT_VIN/3: R2.1, R4.2, U1.~AD31
SCALED_BATT_VIN/4: R31.1, R32.2, U10.~AD31
SCALED_BATT_VIN/5: R40.1, R41.2, U13.~AD31
SCALED_BATT_VIN/6: R49.1, R50.2, U16.~AD31
SCALED_BATT_VIN/7: R58.1, R59.2, U19.~AD31
SCALED_BATT_VIN/8: R67.1, R68.2, U22.~AD31
SCALED_BATT_VIN/9: R76.1, R77.2, U25.~AD31
SCALED_BATT_VIN/10: R85.1, R86.2, U28.~AD31
SCALED_BATT_VIN/11: R94.1, R95.2, U31.~AD31
SCALED_BATT_VIN/12: R103.1, R104.2, U34.~AD31
SCALED_BATT_VIN/13: R112.1, R113.2, U37.~AD31
SCALED_BATT_VIN/14: R121.1, R122.2, U40.~AD31
SCALED_BATT_VIN/15: R130.1, R131.2, U43.~AD31
SCALED_BATT_VIN/16: R139.1, R140.2, U46.~AD31
SCL: J1.14, U1.~D39
SCL1: J1.53, U1.D8
SCL2: J2.14, U3.~D39
SCL3: J2.53, U3.D8
SCL4: J3.14, U7.~D39
SCL5: J3.53, U7.D8
SCL6: J4.14, U10.~D39
SCL7: J4.53, U10.D8
SCL8: J5.14, U13.~D39
SCL9: J5.53, U13.D8
SCL10: J6.14, U16.~D39
SCL11: J6.53, U16.D8
SCL12: J7.14, U19.~D39
SCL13: J7.53, U19.D8
SCL14: J8.14, U22.~D39
SCL15: J8.53, U22.D8
SCL16: J9.14, U25.~D39
SCL17: J9.53, U25.D8
SCL18: J10.14, U28.~D39
SCL19: J10.53, U28.D8
SCL20: J11.14, U31.~D39
SCL21: J11.53, U31.D8
SCL22: J12.14, U34.~D39
SCL23: J12.53, U34.D8
SCL24: J13.14, U37.~D39
SCL25: J13.53, U37.D8
SCL26: J14.14, U40.~D39
SCL27: J14.53, U40.D8
SCL28: J15.14, U43.~D39
SCL29: J15.53, U43.D8
SCL30: J16.14, U46.~D39
SCL31: J16.53, U46.D8
SDA: J1.12, U1.D40
SDA1: J1.51, U1.D9
SDA2: J2.12, U3.D40
SDA3: J2.51, U3.D9
SDA4: J3.12, U7.D40
SDA5: J3.51, U7.D9
SDA6: J4.12, U10.D40
SDA7: J4.51, U10.D9
SDA8: J5.12, U13.D40
SDA9: J5.51, U13.D9
SDA10: J6.12, U16.D40
SDA11: J6.51, U16.D9
SDA12: J7.12, U19.D40
SDA13: J7.51, U19.D9
SDA14: J8.12, U22.D40
SDA15: J8.51, U22.D9
SDA16: J9.12, U25.D40
SDA17: J9.51, U25.D9
SDA18: J10.12, U28.D40
SDA19: J10.51, U28.D9
SDA20: J11.12, U31.D40
SDA21: J11.51, U31.D9
SDA22: J12.12, U34.D40
SDA23: J12.51, U34.D9
SDA24: J13.12, U37.D40
SDA25: J13.51, U37.D9
SDA26: J14.12, U40.D40
SDA27: J14.51, U40.D9
SDA28: J15.12, U43.D40
SDA29: J15.51, U43.D9
SDA30: J16.12, U46.D40
SDA31: J16.51, U46.D9
SPI_!CS1!/QSPI1: J2.70, U3.~D23
SPI_!CS1!/QSPI2: J3.70, U7.~D23
SPI_!CS1!/QSPI3: J1.70, U1.~D23
SPI_!CS1!/QSPI4: J4.70, U10.~D23
SPI_!CS1!/QSPI5: J5.70, U13.~D23
SPI_!CS1!/QSPI6: J6.70, U16.~D23
SPI_!CS1!/QSPI7: J7.70, U19.~D23
SPI_!CS1!/QSPI8: J8.70, U22.~D23
SPI_!CS1!/QSPI9: J9.70, U25.~D23
SPI_!CS1!/QSPI10: J10.70, U28.~D23
SPI_!CS1!/QSPI11: J11.70, U31.~D23
SPI_!CS1!/QSPI12: J12.70, U34.~D23
SPI_!CS1!/QSPI13: J13.70, U37.~D23
SPI_!CS1!/QSPI14: J14.70, U40.~D23
SPI_!CS1!/QSPI15: J15.70, U43.~D23
SPI_!CS1!/QSPI16: J16.70, U46.~D23
SPI_!CS!: J1.55, U1.D41
SPI_!CS!1: J2.55, U3.D41
SPI_!CS!2: J3.55, U7.D41
SPI_!CS!3: J4.55, U10.D41
SPI_!CS!4: J5.55, U13.D41
SPI_!CS!5: J6.55, U16.D41
SPI_!CS!6: J7.55, U19.D41
SPI_!CS!7: J8.55, U22.D41
SPI_!CS!8: J9.55, U25.D41
SPI_!CS!9: J10.55, U28.D41
SPI_!CS!10: J11.55, U31.D41
SPI_!CS!11: J12.55, U34.D41
SPI_!CS!12: J13.55, U37.D41
SPI_!CS!13: J14.55, U40.D41
SPI_!CS!14: J15.55, U43.D41
SPI_!CS!15: J16.55, U46.D41
SPI_CIPO: J1.61, U1.~D43
SPI_CIPO1: J2.61, U3.~D43
SPI_CIPO1/QSPI0: J1.64, U1.~D6, U1.~D22
SPI_CIPO1/QSPI1: J2.64, U3.~D6, U3.~D22
SPI_CIPO1/QSPI2: J3.64, U7.~D6, U7.~D22
SPI_CIPO1/QSPI3: J4.64, U10.~D6, U10.~D22
SPI_CIPO1/QSPI4: J5.64, U13.~D6, U13.~D22
SPI_CIPO1/QSPI5: J6.64, U16.~D6, U16.~D22
SPI_CIPO1/QSPI6: J7.64, U19.~D6, U19.~D22
SPI_CIPO1/QSPI7: J8.64, U22.~D6, U22.~D22
SPI_CIPO1/QSPI8: J9.64, U25.~D6, U25.~D22
SPI_CIPO1/QSPI9: J10.64, U28.~D6, U28.~D22
SPI_CIPO1/QSPI10: J11.64, U31.~D6, U31.~D22
SPI_CIPO1/QSPI11: J12.64, U34.~D6, U34.~D22
SPI_CIPO1/QSPI12: J13.64, U37.~D6, U37.~D22
SPI_CIPO1/QSPI13: J14.64, U40.~D6, U40.~D22
SPI_CIPO1/QSPI14: J15.64, U43.~D6, U43.~D22
SPI_CIPO1/QSPI15: J16.64, U46.~D6, U46.~D22
SPI_CIPO2: J3.61, U7.~D43
SPI_CIPO3: J4.61, U10.~D43
SPI_CIPO4: J5.61, U13.~D43
SPI_CIPO5: J6.61, U16.~D43
SPI_CIPO6: J7.61, U19.~D43
SPI_CIPO7: J8.61, U22.~D43
SPI_CIPO8: J9.61, U25.~D43
SPI_CIPO9: J10.61, U28.~D43
SPI_CIPO10: J11.61, U31.~D43
SPI_CIPO11: J12.61, U34.~D43
SPI_CIPO12: J13.61, U37.~D43
SPI_CIPO13: J14.61, U40.~D43
SPI_CIPO14: J15.61, U43.~D43
SPI_CIPO15: J16.61, U46.~D43
SPI_COPI: J1.59, U1.D38
SPI_COPI1: J2.59, U3.D38
SPI_COPI1/QSPI_!CS!: J1.62, U1.D7
SPI_COPI1/QSPI_!CS!1: J2.62, U3.D7
SPI_COPI1/QSPI_!CS!2: J3.62, U7.D7
SPI_COPI1/QSPI_!CS!3: J4.62, U10.D7
SPI_COPI1/QSPI_!CS!4: J5.62, U13.D7
SPI_COPI1/QSPI_!CS!5: J6.62, U16.D7
SPI_COPI1/QSPI_!CS!6: J7.62, U19.D7
SPI_COPI1/QSPI_!CS!7: J8.62, U22.D7
SPI_COPI1/QSPI_!CS!8: J9.62, U25.D7
SPI_COPI1/QSPI_!CS!9: J10.62, U28.D7
SPI_COPI1/QSPI_!CS!10: J11.62, U31.D7
SPI_COPI1/QSPI_!CS!11: J12.62, U34.D7
SPI_COPI1/QSPI_!CS!12: J13.62, U37.D7
SPI_COPI1/QSPI_!CS!13: J14.62, U40.D7
SPI_COPI1/QSPI_!CS!14: J15.62, U43.D7
SPI_COPI1/QSPI_!CS!15: J16.62, U46.D7
SPI_COPI2: J3.59, U7.D38
SPI_COPI3: J4.59, U10.D38
SPI_COPI4: J5.59, U13.D38
SPI_COPI5: J6.59, U16.D38
SPI_COPI6: J7.59, U19.D38
SPI_COPI7: J8.59, U22.D38
SPI_COPI8: J9.59, U25.D38
SPI_COPI9: J10.59, U28.D38
SPI_COPI10: J11.59, U31.D38
SPI_COPI11: J12.59, U34.D38
SPI_COPI12: J13.59, U37.D38
SPI_COPI13: J14.59, U40.D38
SPI_COPI14: J15.59, U43.D38
SPI_COPI15: J16.59, U46.D38
SPI_SCK: J1.57, U1.~D42
SPI_SCK1: J2.57, U3.~D42
SPI_SCK1/QSPI_SCK: J1.60, U1.~D5, U1.~D24
SPI_SCK1/QSPI_SCK1: J2.60, U3.~D5, U3.~D24
SPI_SCK1/QSPI_SCK2: J3.60, U7.~D5, U7.~D24
SPI_SCK1/QSPI_SCK3: J4.60, U10.~D5, U10.~D24
SPI_SCK1/QSPI_SCK4: J5.60, U13.~D5, U13.~D24
SPI_SCK1/QSPI_SCK5: J6.60, U16.~D5, U16.~D24
SPI_SCK1/QSPI_SCK6: J7.60, U19.~D5, U19.~D24
SPI_SCK1/QSPI_SCK7: J8.60, U22.~D5, U22.~D24
SPI_SCK1/QSPI_SCK8: J9.60, U25.~D5, U25.~D24
SPI_SCK1/QSPI_SCK9: J10.60, U28.~D5, U28.~D24
SPI_SCK1/QSPI_SCK10: J11.60, U31.~D5, U31.~D24
SPI_SCK1/QSPI_SCK11: J12.60, U34.~D5, U34.~D24
SPI_SCK1/QSPI_SCK12: J13.60, U37.~D5, U37.~D24
SPI_SCK1/QSPI_SCK13: J14.60, U40.~D5, U40.~D24
SPI_SCK1/QSPI_SCK14: J15.60, U43.~D5, U43.~D24
SPI_SCK1/QSPI_SCK15: J16.60, U46.~D5, U46.~D24
SPI_SCK2: J3.57, U7.~D42
SPI_SCK3: J4.57, U10.~D42
SPI_SCK4: J5.57, U13.~D42
SPI_SCK5: J6.57, U16.~D42
SPI_SCK6: J7.57, U19.~D42
SPI_SCK7: J8.57, U22.~D42
SPI_SCK8: J9.57, U25.~D42
SPI_SCK9: J10.57, U28.~D42
SPI_SCK10: J11.57, U31.~D42
SPI_SCK11: J12.57, U34.~D42
SPI_SCK12: J13.57, U37.~D42
SPI_SCK13: J14.57, U40.~D42
SPI_SCK14: J15.57, U43.~D42
SPI_SCK15: J16.57, U46.~D42
SWDCK: J1.21, U1.SWDCK
SWDCK1: J2.21, U3.SWDCK
SWDCK2: J3.21, U7.SWDCK
SWDCK3: J4.21, U10.SWDCK
SWDCK4: J5.21, U13.SWDCK
SWDCK5: J6.21, U16.SWDCK
SWDCK6: J7.21, U19.SWDCK
SWDCK7: J8.21, U22.SWDCK
SWDCK8: J9.21, U25.SWDCK
SWDCK9: J10.21, U28.SWDCK
SWDCK10: J11.21, U31.SWDCK
SWDCK11: J12.21, U34.SWDCK
SWDCK12: J13.21, U37.SWDCK
SWDCK13: J14.21, U40.SWDCK
SWDCK14: J15.21, U43.SWDCK
SWDCK15: J16.21, U46.SWDCK
SWDIO: J1.23, U1.SWDIO
SWDIO1: J2.23, U3.SWDIO
SWDIO2: J3.23, U7.SWDIO
SWDIO3: J4.23, U10.SWDIO
SWDIO4: J5.23, U13.SWDIO
SWDIO5: J6.23, U16.SWDIO
SWDIO6: J7.23, U19.SWDIO
SWDIO7: J8.23, U22.SWDIO
SWDIO8: J9.23, U25.SWDIO
SWDIO9: J10.23, U28.SWDIO
SWDIO10: J11.23, U31.SWDIO
SWDIO11: J12.23, U34.SWDIO
SWDIO12: J13.23, U37.SWDIO
SWDIO13: J14.23, U40.SWDIO
SWDIO14: J15.23, U43.SWDIO
SWDIO15: J16.23, U46.SWDIO
TX1/ADC_D-: J1.17, J1.65, U1.~AD12
TX1/ADC_D-1: J2.17, J2.65, U3.~AD12
TX1/ADC_D-2: J3.17, J3.65, U7.~AD12
TX1/ADC_D-3: J4.17, J4.65, U10.~AD12
TX1/ADC_D-4: J5.17, J5.65, U13.~AD12
TX1/ADC_D-5: J6.17, J6.65, U16.~AD12
TX1/ADC_D-6: J7.17, J7.65, U19.~AD12
TX1/ADC_D-7: J8.17, J8.65, U22.~AD12
TX1/ADC_D-8: J9.17, J9.65, U25.~AD12
TX1/ADC_D-9: J10.17, J10.65, U28.~AD12
TX1/ADC_D-10: J11.17, J11.65, U31.~AD12
TX1/ADC_D-11: J12.17, J12.65, U34.~AD12
TX1/ADC_D-12: J13.17, J13.65, U37.~AD12
TX1/ADC_D-13: J14.17, J14.65, U40.~AD12
TX1/ADC_D-14: J15.17, J15.65, U43.~AD12
TX1/ADC_D-15: J16.17, J16.65, U46.~AD12
TXO-0: U1.TXO-0, U6.9
TXO-1: U3.TXO-0, U4.9
TXO-2: U7.TXO-0, U8.9
TXO-3: U10.TXO-0, U11.9
TXO-4: U13.TXO-0, U14.9
TXO-5: U16.TXO-0, U17.9
TXO-6: U19.TXO-0, U20.9
TXO-7: U22.TXO-0, U23.9
TXO-8: U25.TXO-0, U26.9
TXO-9: U28.TXO-0, U29.9
TXO-10: U31.TXO-0, U32.9
TXO-11: U34.TXO-0, U35.9
TXO-12: U37.TXO-0, U38.9
TXO-13: U40.TXO-0, U41.9
TXO-14: U43.TXO-0, U44.9
TXO-15: U46.TXO-0, U47.9
USB_D+: J1.3, U6.1
USB_D+1: J2.3, U4.1
USB_D+2: J3.3, U8.1
USB_D+3: J4.3, U11.1
USB_D+4: J5.3, U14.1
USB_D+5: J6.3, U17.1
USB_D+6: J7.3, U20.1
USB_D+7: J8.3, U23.1
USB_D+8: J9.3, U26.1
USB_D+9: J10.3, U29.1
USB_D+10: J11.3, U32.1
USB_D+11: J12.3, U35.1
USB_D+12: J13.3, U38.1
USB_D+13: J14.3, U41.1
USB_D+14: J15.3, U44.1
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
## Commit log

2020-03-24 Production of v10
2020-03-24 Add ignore
2020-04-08 Adding panel files for v10
2020-04-08 v11 adds ADC buffers, 3.3V enable, RTC backup power, 0402 components.
2020-04-15 Routed CAM_PCLK
2020-04-15 Double buffered ADC.
2020-04-15 Add v1.1 production files
2020-05-04 Add reverse diode to prevent RTC 3.3V from driving 3.3V bus. Add test sketches.
2020-05-08 Add MicroMod logo, double route MCLK.
2020-05-08 Add MicroMod logo.
2020-05-13 Route from opamp for better AOI. fix DRC error. Add v1.2 panel files.
2020-05-20 File rename
2020-06-08 Add missing net to Xtal
2020-06-08 Adding v13 production files
2020-06-18 Fix SDA1/SCL1, CS1, and VIN/3 incorrect pin locations.
2020-06-18 Roll version to v1.4
2020-06-23 Connect SPI pins to support Quad SPI. Move TX1 to AD12
2020-08-13 Adding additional decoupling, change version to v16.
2020-10-01 Update SPI port 0/1 net names.
2020-10-02 Change 3.3V back feed diode to lower v-drop.
2020-10-03 Move CH340 to 3.3V side of diode. Replace D7 with 0.3uA leakage diode.
2020-10-05 Adding v17 production files
